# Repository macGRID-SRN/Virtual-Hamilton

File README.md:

# Virtual-Hamilton
For all things related to Virtual Hamilton

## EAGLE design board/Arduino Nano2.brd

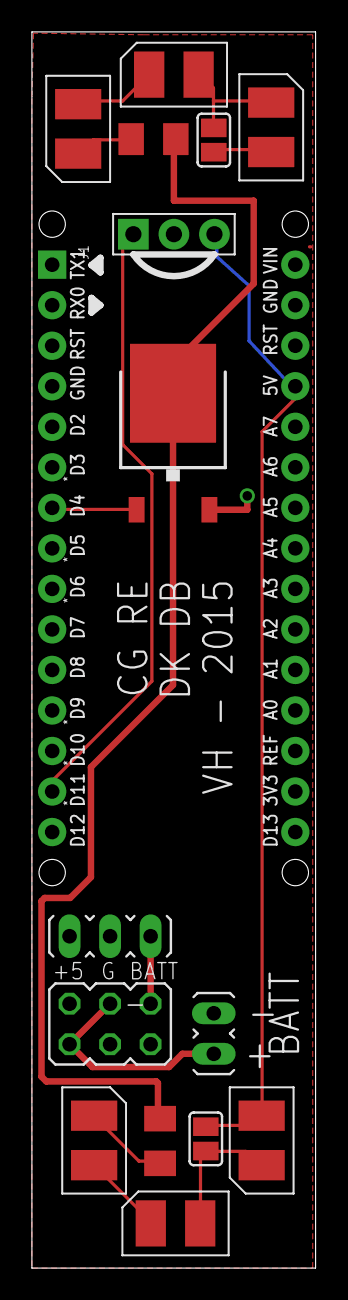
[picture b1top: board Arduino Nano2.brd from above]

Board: 2 copper layers, 17.8 x 77.5 mm, 17 parts (0 on the bottom side), 13 nets.

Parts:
J1: HEAD15-NOSS
J2: HEAD15-NOSS-1
JP1: JP2
JP2: JP3Q
JP3: JP1
Q1: SPD30P06PTO252; TO252
R1, R2: M1206
SJ1, SJ2: SJ
U$1, U$2, U$3, U$4, U$5, U$6: SMD-LED-PLCC-2; PLCC-2
U$7: PNA460XM

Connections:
D4: J1.7, Q1.1
D11/MOSI: J1.14, U$7.1
GND: J2.2, JP1.2, JP2.5, JP3.2, Q1.2, U$7.2
unnamed: Q1.3, R1.2, R2.2
unnamed: J2.4, JP1.1, SJ1.2, SJ2.2, U$3.PPOS, U$6.PPOS, U$7.3
unnamed: R2.1, U$1.PGND
unnamed: R1.1, U$4.PGND
unnamed: U$1.PPOS, U$2.PGND
unnamed: SJ2.1, U$2.PPOS, U$3.PGND
unnamed: U$4.PPOS, U$5.PGND
unnamed: SJ1.1, U$5.PPOS, U$6.PGND
unnamed: JP1.3, JP2.6
unnamed: JP2.1, JP2.4, JP3.1

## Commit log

2015-06-17 init commit
2015-06-23 added basic object tracking and synching to text file
2015-08-16 Prepped for focus groups, changed back to ir system
2015-08-16 removed useless files
2015-08-16 added untracked files
2015-08-16 added initial arduino code files
2015-08-16 fixed folder structure
2015-09-26 slave and master now working
2015-09-28 added initial board footprint with nano pinout
2015-10-01 updated IR led code
2015-10-01 initial commit of rob's charting softwares
2015-10-01 grid sending formatting updated to new format
2015-10-05 additional battery components added to board
2015-10-05 undid airroute - added power polygons
2015-10-05 finalized design minus silk screen
2015-10-05 updated git ignore for silly osx files. whoops
2015-10-11 added gerber and updated design for production
